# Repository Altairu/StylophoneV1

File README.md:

# StylophoneV1
StylophoneV1
https://x.com/Flying___eagle/status/1730945111239131318?s=20

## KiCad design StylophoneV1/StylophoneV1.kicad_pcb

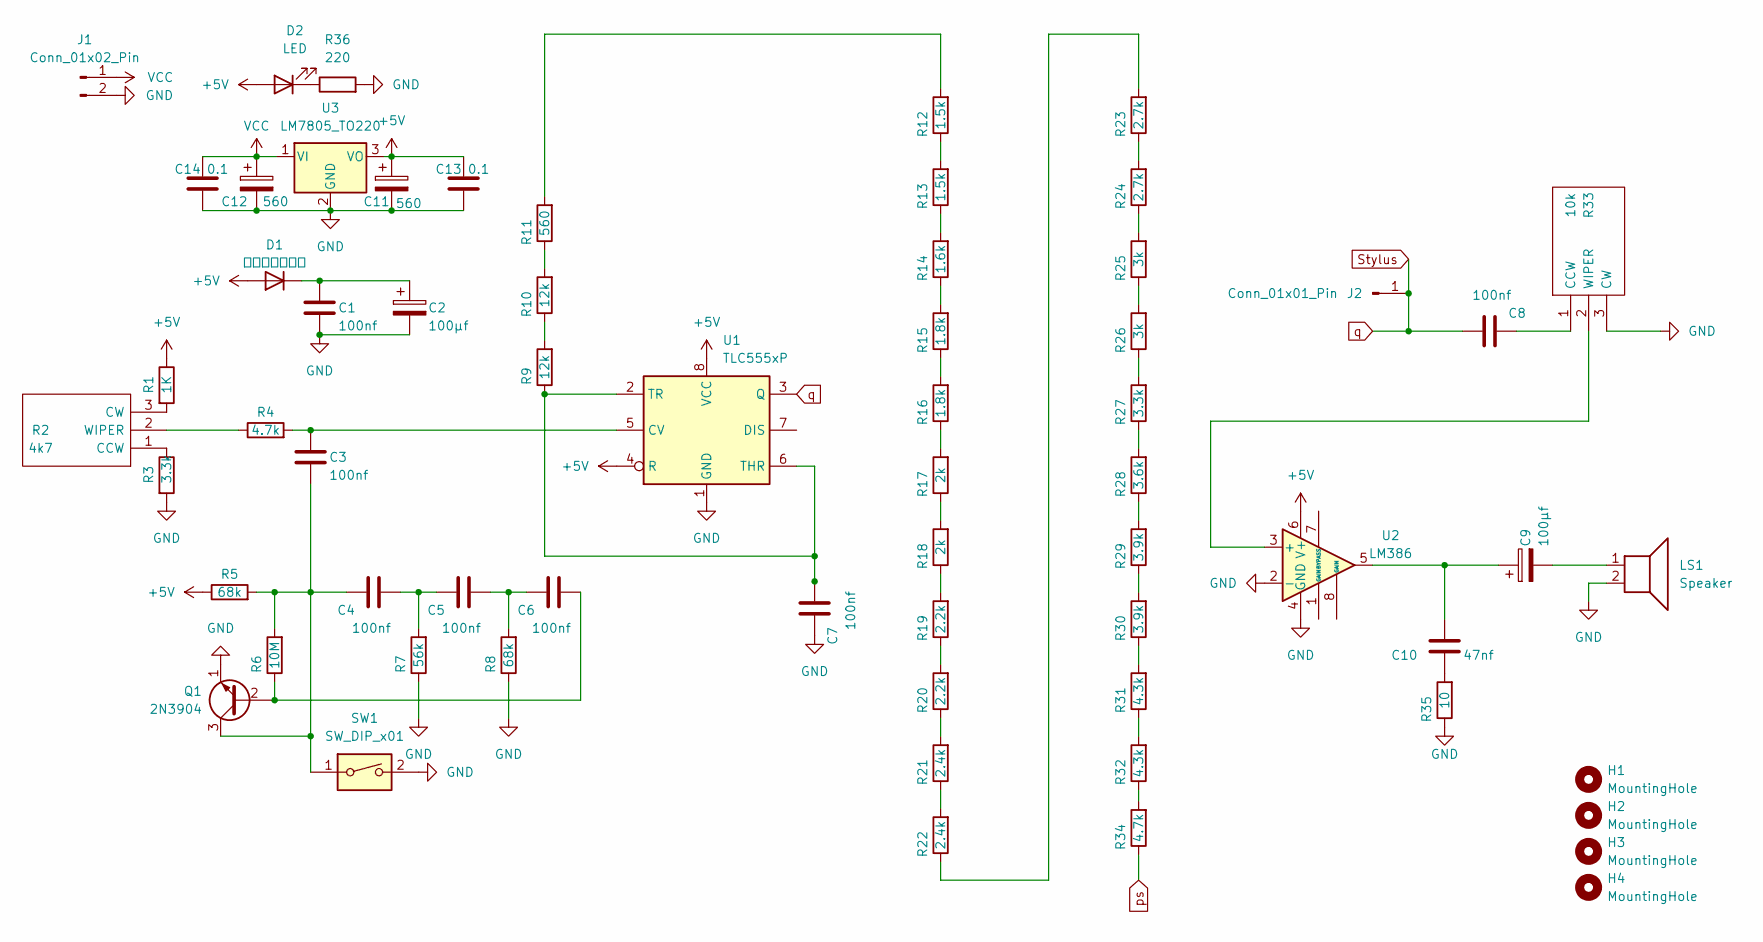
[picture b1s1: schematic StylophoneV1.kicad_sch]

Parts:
C1, C3, C4, C5, C6, C7, C8: 100nf; C_Disc_D8.0mm_W2.5mm_P5.00mm
C2: 100μf; CP_Radial_D10.0mm_P2.50mm
C9: 100μf; CP_Radial_D10.0mm_P3.50mm
C10: 47nf; C_Disc_D8.0mm_W2.5mm_P5.00mm
C11, C12: 560; CP_Radial_D10.0mm_P3.50mm
C13, C14: 0.1; C_Disc_D8.0mm_W2.5mm_P5.00mm
D1: １Ｎ４００７Ｇ; TO-220-2_Vertical
D2: LED; LED_D3.0mm
H1, H2, H3, H4: MountingHole; MountingHole_3.2mm_M3
J1: Conn_01x02_Pin; PinHeader_1x02_P2.54mm_Vertical
J2: Conn_01x01_Pin; PinHeader_1x01_P2.54mm_Vertical
LS1: Speaker; PinHeader_1x02_P2.54mm_Vertical
Q1: 2N3904; TO-92_Inline
R1: 1K; R_Axial_DIN0207_L6.3mm_D2.5mm_P10.16mm_Horizontal
R2: 4k7; 3296W-1; Manufacturer_Part_Number 3296W-1-503LF; Mouser Part Number 652-3296W-1-503LF
R3, R27: 3.3k; R_Axial_DIN0207_L6.3mm_D2.5mm_P10.16mm_Horizontal
R4, R34: 4.7k; R_Axial_DIN0207_L6.3mm_D2.5mm_P10.16mm_Horizontal
R5, R8: 68k; R_Axial_DIN0207_L6.3mm_D2.5mm_P10.16mm_Horizontal
R6: 10M; R_Axial_DIN0207_L6.3mm_D2.5mm_P10.16mm_Horizontal
R7: 56k; R_Axial_DIN0207_L6.3mm_D2.5mm_P10.16mm_Horizontal
R9, R10: 12k; R_Axial_DIN0207_L6.3mm_D2.5mm_P10.16mm_Horizontal
R11: 560; R_Axial_DIN0207_L6.3mm_D2.5mm_P10.16mm_Horizontal
R12, R13: 1.5k; R_Axial_DIN0207_L6.3mm_D2.5mm_P10.16mm_Horizontal
R14: 1.6k; R_Axial_DIN0207_L6.3mm_D2.5mm_P10.16mm_Horizontal
R15, R16: 1.8k; R_Axial_DIN0207_L6.3mm_D2.5mm_P10.16mm_Horizontal
R17, R18: 2k; R_Axial_DIN0207_L6.3mm_D2.5mm_P10.16mm_Horizontal
R19, R20: 2.2k; R_Axial_DIN0207_L6.3mm_D2.5mm_P10.16mm_Horizontal
R21, R22: 2.4k; R_Axial_DIN0207_L6.3mm_D2.5mm_P10.16mm_Horizontal
R23, R24: 2.7k; R_Axial_DIN0207_L6.3mm_D2.5mm_P10.16mm_Horizontal
R25, R26: 3k; R_Axial_DIN0207_L6.3mm_D2.5mm_P10.16mm_Horizontal
R28: 3.6k; R_Axial_DIN0207_L6.3mm_D2.5mm_P10.16mm_Horizontal
R29, R30: 3.9k; R_Axial_DIN0207_L6.3mm_D2.5mm_P10.16mm_Horizontal
R31, R32: 4.3k; R_Axial_DIN0207_L6.3mm_D2.5mm_P10.16mm_Horizontal
R33: 10k; 3296W-1; Manufacturer_Part_Number 3296W-1-503LF; Mouser Part Number 652-3296W-1-503LF
R35: 10; R_Axial_DIN0207_L6.3mm_D2.5mm_P10.16mm_Horizontal
R36: 220; R_Axial_DIN0207_L6.3mm_D2.5mm_P10.16mm_Horizontal
SW1: SW_DIP_x01; PinHeader_1x02_P2.54mm_Vertical
U1: TLC555xP; DIP-8_W7.62mm
U2: LM386; DIP-8_W7.62mm
U3: LM7805_TO220; TO-220-3_Vertical

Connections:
+5V: C11.1, C13.1, D1.2 (A), D2.2 (A), R1.1, R5.1, U1.4 (R), U1.8 (VCC), U2.6 (V+), U3.3 (VO)
GND: C1.2, C2.2, C7.1, C11.2, C12.2, C13.2, C14.2, J1.2, LS1.2, Q1.1 (E), R3.2, R7.1, R8.1, R33.3 (CW), R35.1, R36.2, SW1.2, U1.1 (GND), U2.2 (-), U2.4 (GND), U3.2 (GND)
unnamed: C4.2, C5.1, R7.2
unnamed: C5.2, C6.1, R8.2
unnamed: C9.2, LS1.1
unnamed: C9.1, C10.1, U2.5
unnamed: C10.2, R35.2
unnamed: C1.1, C2.1, D1.1 (K)
unnamed: D2.1 (K), R36.1
unnamed: C6.2, Q1.2 (B), R6.1
unnamed: C3.2, C4.1, Q1.3 (C), R5.2, R6.2, SW1.1
unnamed: R2.1 (CCW), R3.1
unnamed: R1.2, R2.3 (CW)
unnamed: R2.2 (WIPER), R4.1
unnamed: R9.2, R10.1
unnamed: R10.2, R11.1
unnamed: R11.2, R12.2
unnamed: R12.1, R13.2
unnamed: R13.1, R14.2
unnamed: R14.1, R15.2
unnamed: R15.1, R16.2
unnamed: R16.1, R17.2
unnamed: R17.1, R18.2
unnamed: R18.1, R19.2
unnamed: R19.1, R20.2
unnamed: R20.1, R21.2
unnamed: R21.1, R22.2
unnamed: R22.1, R23.2
unnamed: R23.1, R24.2
unnamed: R24.1, R25.2
unnamed: R25.1, R26.2
unnamed: R26.1, R27.2
unnamed: R27.1, R28.2
unnamed: R28.1, R29.2
unnamed: R29.1, R30.2
unnamed: R30.1, R31.2
unnamed: R31.1, R32.2
unnamed: R32.1, R34.2
unnamed: C8.1, R33.1 (CCW)
unnamed: R33.2 (WIPER), U2.3 (+)
unnamed: C3.1, R4.2, U1.5 (CV)
unnamed: C7.2, R9.1, U1.2 (TR), U1.6 (THR)
Stylus: C8.2, J2.1, U1.3 (Q)
VCC: C12.1, C14.1, J1.1, U3.1 (VI)
ps: R34.1

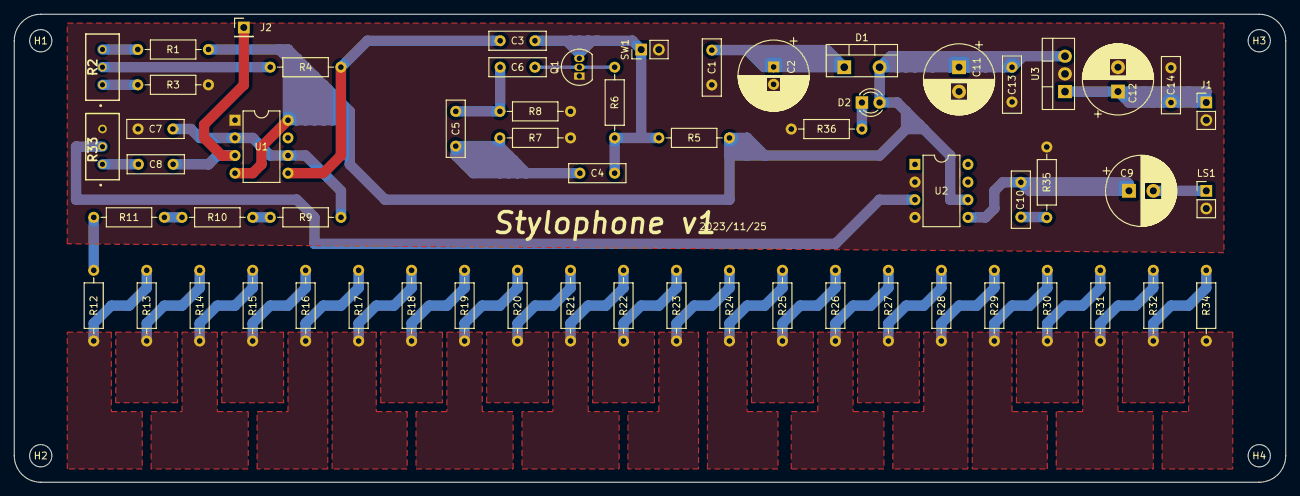
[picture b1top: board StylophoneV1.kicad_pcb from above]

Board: 2 copper layers, 182.9 x 67.3 mm, 64 parts (0 on the bottom side), 44 nets.
